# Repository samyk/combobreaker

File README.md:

# [C-C-C-C-Combo Breaker](http://samy.pl/combobreaker/)

**[Combo Breaker](http://samy.pl/combobreaker/)** is a motorized, battery powered, 3D printed, Arduino-based combination lock cracking device. It is portable, open source, 3D models provided, and exploits a new technique I've discovered for [cracking combination locks in 8 attempts or less](https://www.youtube.com/watch?v=09UgmwtL12c), but in an even more exciting, automated fashion.

By [@SamyKamkar](https://twitter.com/samykamkar)

#### Follow me on [Twitter](https://twitter.com/samykamkar) or [join my mailing list](http://samy.pl/list/) to hear about future projects and research.

**Live demonstration** and full details available in [the video](https://www.youtube.com/watch?v=YcpSvHpbHQ4):

-----

**Point of Contact:** [@SamyKamkar](https://twitter.com/samykamkar) // <http://samy.pl>

**Video demonstration / explanation:** [https://youtu.be/YcpSvHpbHQ4](https://youtu.be/YcpSvHpbHQ4)

**Released:** May 14, 2015

**Source code / 3D models:** [https://github.com/samyk/combobreaker](https://github.com/samyk/combobreaker)

**Unit Cost:** < $100

**Status:** Operational, open source, open hardware, declassified.

-----

# (U) Hardware

### [Arduino Nano](http://amzn.to/1QLlf23)
**$12**: A [5V Arduino Nano](http://amzn.to/1QLlf23) microcontroller is used as the brains of the project.

### [Allegro A3967 / EasyDriver Stepper Driver](http://amzn.to/1A1Ovxl)
**$20**: I originally used an A3967-based [EasyDriver](http://amzn.to/1A1Ovxl) which can drive a stepper motor up to 30V at 750mA. This is what precisely controls the dial.

### or [Allegro A4988](http://amzn.to/1L3q7fK)
**$7**: Instead of the EasyDriver, I upgraded to a smaller, yet more powerful stepper driver that can go up to 1 amp (1000mA).

### [Stepper Motor](http://amzn.to/1FfLUQG)
**$30**: You can use a normal stepper motor for the "simpler" version of the Combo Breaker build, however if you're working on creating the more advanced version, you'll need a double-shaft stepper motor like I liste below.

### or [Double Shaft Stepper Motor](http://www.phidgets.com/products.php?product_id=3320)
**$16**: This double shaft stepper motor allows you to build the more advanced Combo Breaker while employing an optical rotary encoder on the back to detect the position of the stepper when the dial stops turning (which is part of the exploit employed).

### [HKT22 Optical Rotary Encoder](http://www.phidgets.com/products.php?product_id=3531)
**$25**: For use **only** with the double shaft stepper motor, this optical rotary encoder lets us know what position the shaft of the stepper motor is at and allows us to employ an exploit on Master combination locks where the stepper will get locked into certain grooves within the internal combination disc of the lock.

### [Analog Feedback Servo](https://www.adafruit.com/products/1404)
**$15**: This servo not only provides the torque we need to lift the shackle (90.26 oz*in), but has an additional wire providing analog feedback that we use to detect the state of the shackle and whether it has opened or not.

### [L7805 Voltage Regulators](http://amzn.to/1A28XOt)
**$6**: If you're using the analog feedback servo, you'll want to use an external voltage regulator to provide enough juice to the servo. While the Arduino is 5V and can drive the servo normally, it won't be able to pump out enough current for the servo when it starts hitting the shackle and could damage your Arduino.

### [500mAh 3S Lipo Battery](http://amzn.to/1PkRVlz)
**$20**: This 500mAh 3S (3-cell, 11.1V) battery gives enough juice to the stepper motor to be very effective, and at 500mAh can last between 30-120minutes straight before having to be recharged.

### [Lipo Charger](http://amzn.to/1A1Q2n7)
**$50**: This lipo charger is overkill if only used for this project, but is a good one that I use at home for a wide range of batteries and cells. You don't need this one, but if you want to recharge the battery, you'll need a charger that supports 3-cell LiPos.

### [Arctic Alumina Thermal Adehsive](http://amzn.to/1PkTakG)
**$8**: Not required, but this is the thermal **adhesive** I use to **permanently** attach the heatsink to the stepper motor driver. Normal thermal paste has very little adhesion and kept falling off, so I switched from thermal paste to this thermal adhesive.

### [Digital Calipers](http://amzn.to/1K8juex)
**$16**: If you don't already have digital calipers for precise measurements to measure the lock, for example, these are inexpensive and accurate.

### [Breadboard and Wires](http://amzn.to/1FfMb6e)
**$6**: If you don't already have a breadboard and wires, they will kind of help.

-----

# (U) Software

### Combo Breaker
Combo Breaker's source code can be obtained in entirety from my github: <https://github.com/samyk/combobreaker>

-----

# (U) 3D Models

I've included the 3D models on my github: <https://github.com/samyk/combobreaker>

-----

# (U) Contact

**Point of Contact:** [@SamyKamkar](https://twitter.com/samykamkar)

You can see more of my projects at <http://samy.pl>.

#### Follow me on [Twitter](https://twitter.com/samykamkar) or [join my mailing list](http://samy.pl/list/) to hear about future projects and research.

Thanks!

------

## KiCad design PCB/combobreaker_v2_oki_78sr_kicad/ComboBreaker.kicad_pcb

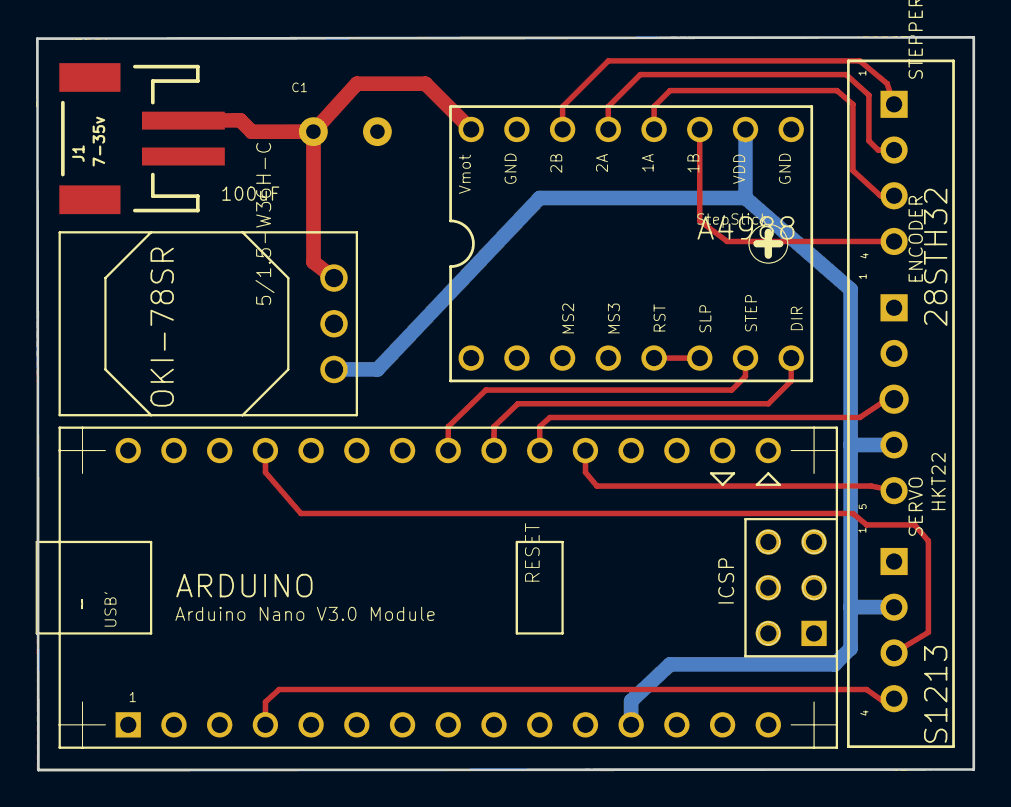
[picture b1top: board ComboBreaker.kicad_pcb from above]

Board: 2 copper layers, 52.0 x 40.7 mm, 8 parts (0 on the bottom side), 14 nets.

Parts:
A4988: StepStick; A4988BREAKOUT
ARDUINO: Arduino Nano V3.0 Module; ARDUINO_NANO
C1: 100uF; E3,5-8
ENCODER: HKT22; MA05-1
J1: 7-35v; JST-2-SMD
OKI-78SR: 5/1.5-W36H-C; OKI-78SRH
SERVO: S1213; MA04-1
STEPPER: 28STH32; MA04-1

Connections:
1A_BLK: A4988.1B, STEPPER.4
1B_GRN: A4988.1A, STEPPER.3
2A_RED: A4988.2A, STEPPER.2
2B_BLU: A4988.2B, STEPPER.1
+5V: A4988.VDD, ARDUINO.12, ENCODER.4, OKI-78SR.3, SERVO.2
D2_CH_A_WHITE: ARDUINO.20, ENCODER.5
D3_CH_B_BROWN: ARDUINO.21, ENCODER.3
D9_SERVO: ARDUINO.27, SERVO.3
FEEDBACK: ARDUINO.4, SERVO.4
GND: A4988.GND, ARDUINO.14, ARDUINO.19, C1.-, ENCODER.1, J1.1, OKI-78SR.2, SERVO.1
unnamed: A4988.RST, A4988.SLP
unnamed: A4988.DIR, ARDUINO.22
unnamed: A4988.STEP, ARDUINO.23
VCC: A4988.VMOT, C1.+, J1.2, OKI-78SR.1

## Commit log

2015-05-14 Added code + 3d models
2015-05-14 finishing up rest
2015-05-14 new pretty pictures
2015-05-14 fixed date
2015-05-14 mo money mo gitcommits
2015-05-17 added f3d (fusion 360 archive file) for the chassis
2015-05-17 added f3d (fusion 360 archive file) for pancake stepper gripper
2015-08-03 Initial Commit
    Still requires verification and testing. Do not build until tested!
2015-08-03 added picture
2015-08-03 Finished Design
    Added Encoder header and verified design against documentation.
    releasing for first piece prototype. please report any errors.
2015-08-04 prettied up
    prettied things up and added some pictures and BOM
2015-08-04 Added Standoff Holes
    #4 Philips standoff holes added to board
2015-08-04 added stl files
    stl files added for 3d printing
2016-11-13 Update prices
2017-03-15 PCB with OKI-78SR
    * Corrected pinouts for LM7805
    * Replaced LM7805 with OKI-78SR switching regulator. This is a “No heat
    sink” direct replacement for 3-terminal 78xx-series linear regulators.
    * Added 100uf decoupling capacitor
    * Updated Arduino Nano device/footprint
    * Updated A4988 StepStep device/footprint
2017-03-15 PCB with LM7805
    * Added decoupling capacitor
    * Updated Arduino Nano device/footprint
    * Updated A4988 StepStep device/footprint
    * Added trace between RST and SLP on A4988
    * Corrected pinouts for LM7805
2017-03-15 PCB with OKI-78SR
    *** Converted EAGLE files to kicad ***
    * Replaced LM7805 with OKI-78SR switching regulator. This is a “No heat
    sink” direct replacement for 3-terminal 78xx-series linear regulators.
    * Added 100uf decoupling capacitor
    * Updated Arduino Nano device/footprint
    * Updated A4988 StepStep device/footprint
2017-03-16 Added I2C OLED Display
    * Added I2C header pins for OLED display
    * Reoriented JST power connector
    * Rerouted VCC
2017-03-19 Updated v2 Eagle PCB layout
    * Added standoff holes
    * Added descriptions
    * Added mitre to board corners
2017-03-19 Updated PCB
    * Moved silkscreen text to tPlace layer
    * Moved holes in Arduino Nano module to Reference layer
2017-03-20 Updated v2 Eagle PCB
    * Added more silkscreen details
    * Minor adjustments to footprints
    TO-DO:
    * Confirm pinout wire colors
2017-03-20 Updated v2 Eagle PCB (Prototype Ordered!)
    This is final prototype design sent to printers!
    * Added Master Lock logo
    * Added pinout wire colors to bottom silkscreen
    * Added pin identifiers to servo/stepper/encoder pins on top silkscreen
    * Redraw ground pour polygons
2017-03-23 Set theme jekyll-theme-minimal
2017-03-31 Update v2 Eagle PCB
    * Fix drill hole size on header pin package
2017-04-05 Updated v2 Eagle PCB
    * Renamed Stepper pinout labels
    * Added ground connections
    * Manually set MIN_DELAY
2017-05-08 Updated ComboBreaker.ino code
    * Corrected DIR and STEP pins
    * Added delayMicroseconds(MIN_DELAY); to line 362 which resolved the
    issue with the stepper motor not stepping correctly
2017-09-06 Replace mod() with % operator
2017-09-25 Added GND pour to TOP layer
    *** Added GND pour to TOP layer to resolve issues with SMD JST connector etc.
    *** Adjusted JST connector pin name to GND.
2017-09-25 Minor changes to schematic
2017-09-28 Updated header pins to circles from ovals
2017-10-05 Updated drill size to .35
    * Updated drill sizes on most holes to .35
    * Adjusted Mini-B USB connector outline on Arduino Nano silkscreen
2017-10-06 v3 PCB
    Minor changes
    V3 send to fabrication
2018-12-22 VSCode
2018-12-22 Adding .DS_Store to ignore list
2019-04-08 Adding .DS_Store
